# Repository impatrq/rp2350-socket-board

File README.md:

# rp2350-socket-board
Repositorio de la placa de adaptación para el RP2350

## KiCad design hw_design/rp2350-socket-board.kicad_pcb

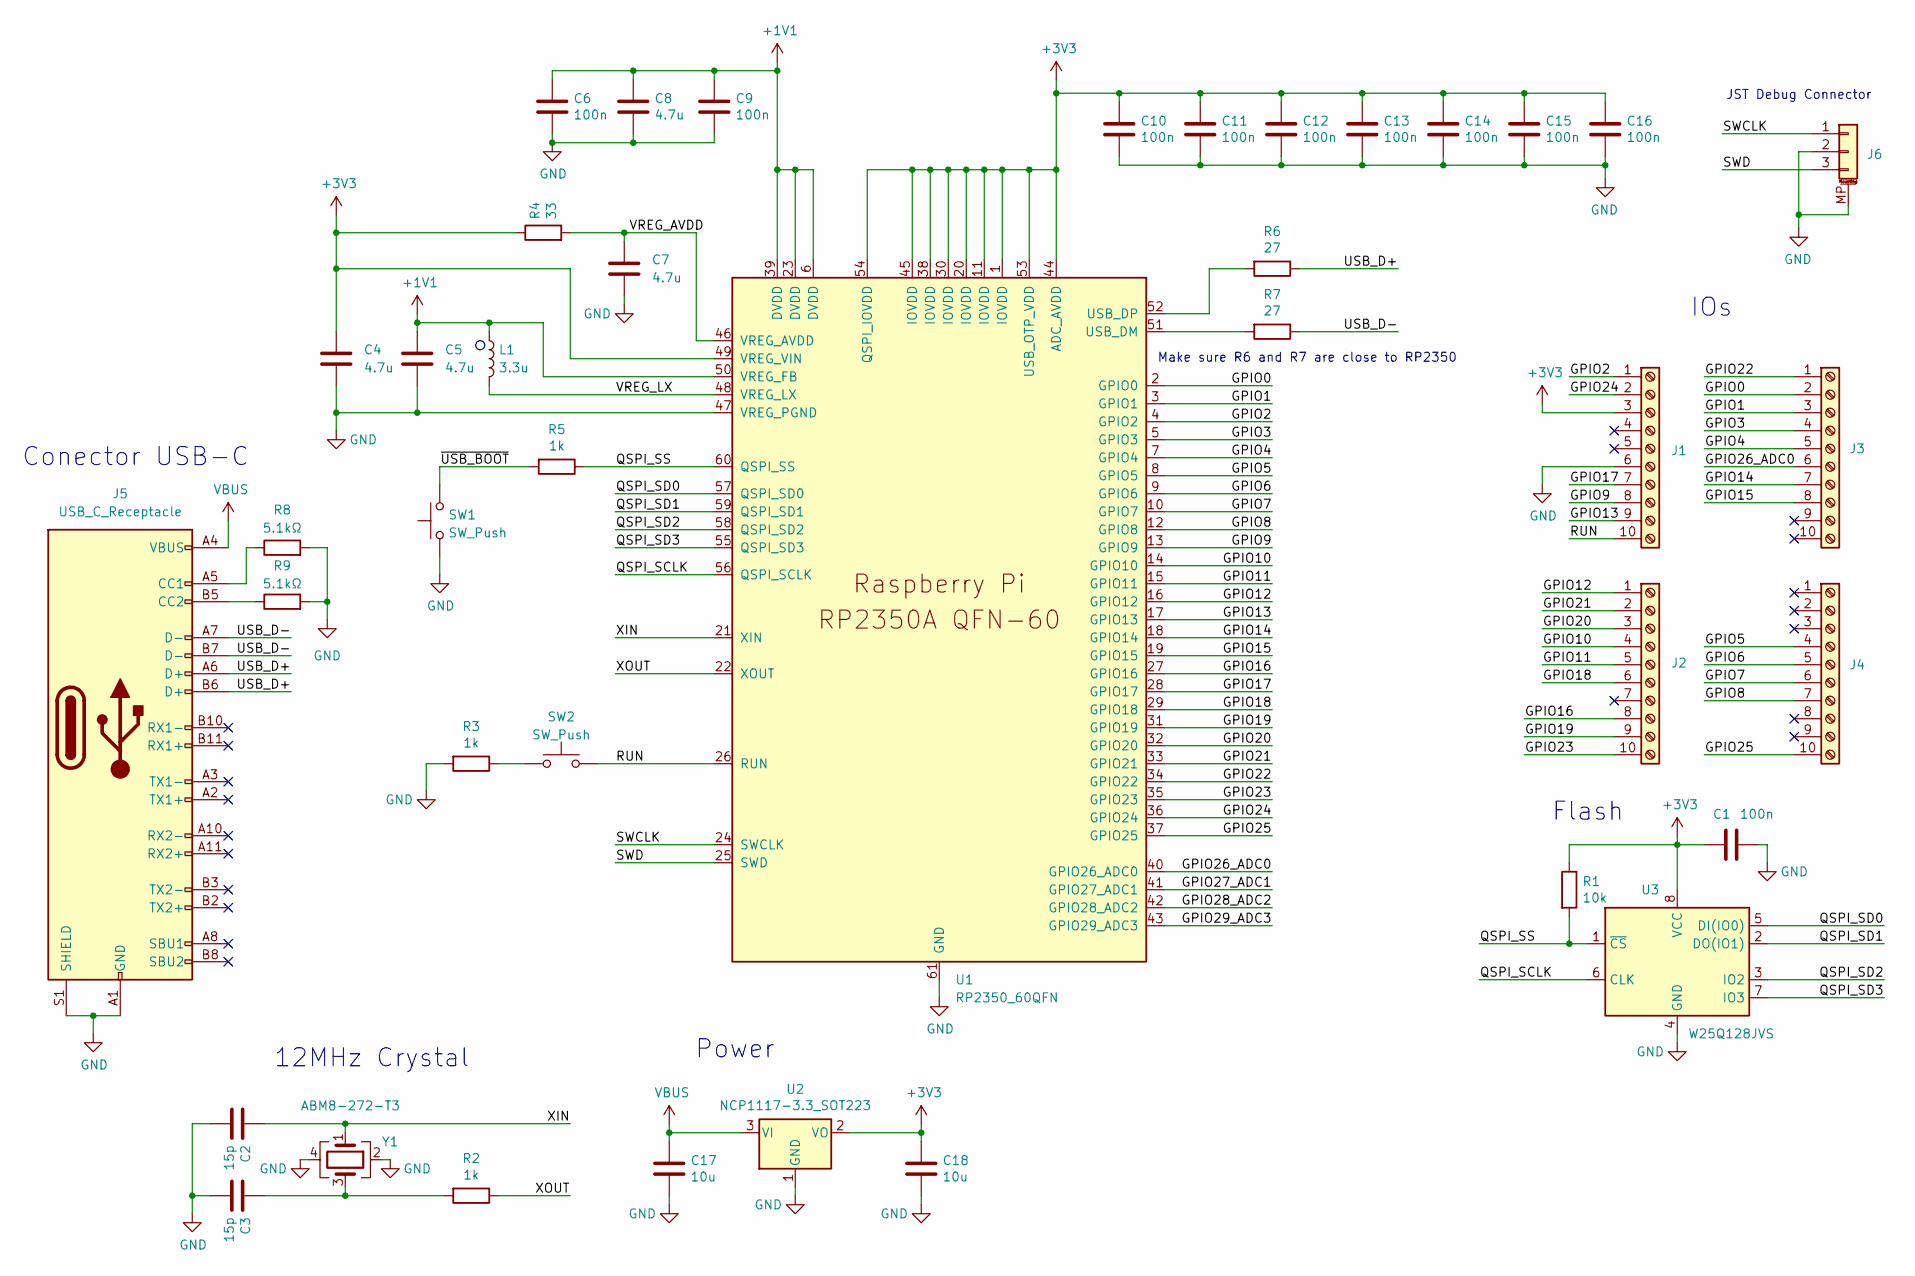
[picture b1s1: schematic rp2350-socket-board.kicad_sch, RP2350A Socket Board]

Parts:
C1, C6, C9, C10, C11, C12, C13, C14, C15, C16: 100n; C_0402_1005Metric_Pad0.74x0.62mm_HandSolder
C2, C3: 15p; C_0402_1005Metric_Pad0.74x0.62mm_HandSolder
C4, C5: 4.7u; C_0402_1005Metric_small_pads
C7, C8: 4.7u; C_0402_1005Metric_Pad0.74x0.62mm_HandSolder
C17, C18: 10u; C_0402_1005Metric_Pad0.74x0.62mm_HandSolder
J1, J2, J3, J4: Screw_Terminal_01x10; PinHeader_1x10_P2.54mm_Vertical
J5: USB_C_Receptacle; USB_C_Receptacle_G-Switch_GT-USB-7010ASV
J6: SM03B-SRSS-TB; PinHeader_1x03_P2.54mm_Vertical
L1: 3.3u; L_pol_2016
R1: 10k; R_0402_1005Metric
R2, R3, R5: 1k; R_0402_1005Metric
R4: 33; R_0402_1005Metric
R6, R7: 27; R_0402_1005Metric
R8, R9: 5.1kΩ; R_0402_1005Metric
SW1, SW2: SW_Push; SW_Push_1P1T_NO_Vertical_Wuerth_434133025816
U1: RP2350_60QFN; RP2350-QFN-60-1EP_7x7_P0.4mm_EP3.4x3.4mm_ThermalVias
U2: NCP1117-3.3_SOT223; SOT-223-3_TabPin2
U3: W25Q128JVS; SOIC-8_5.3x5.3mm_P1.27mm
Y1: ABM8-272-T3; Crystal_SMD_3225-4Pin_3.2x2.5mm

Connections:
+1V1: C5.1, C6.1, C8.1, C9.1, L1.1, U1.6 (DVDD), U1.23 (DVDD), U1.39 (DVDD), U1.50 (VREG_FB)
+3V3: C1.1, C4.1, C10.1, C11.1, C12.1, C13.1, C14.1, C15.1, C16.1, C18.1, J1.3, R1.1, R4.1, U1.1 (IOVDD), U1.11 (IOVDD), U1.20 (IOVDD), U1.30 (IOVDD), U1.38 (IOVDD), U1.44 (ADC_AVDD), U1.45 (IOVDD), U1.49 (VREG_VIN), U1.53 (USB_OTP_VDD), U1.54 (QSPI_IOVDD), U2.2 (VO), U3.8 (VCC)
/GPIO0: J3.2, U1.2 (GPIO0)
/GPIO1: J3.3, U1.3 (GPIO1)
/GPIO2: J1.1, U1.4 (GPIO2)
/GPIO3: J3.4, U1.5 (GPIO3)
/GPIO4: J3.5, U1.7 (GPIO4)
/GPIO5: J4.4, U1.8 (GPIO5)
/GPIO6: J4.5, U1.9 (GPIO6)
/GPIO7: J4.6, U1.10 (GPIO7)
/GPIO8: J4.7, U1.12 (GPIO8)
/GPIO9: J1.8, U1.13 (GPIO9)
/GPIO10: J2.4, U1.14 (GPIO10)
/GPIO11: J2.5, U1.15 (GPIO11)
/GPIO12: J2.1, U1.16 (GPIO12)
/GPIO13: J1.9, U1.17 (GPIO13)
/GPIO14: J3.7, U1.18 (GPIO14)
/GPIO15: J3.8, U1.19 (GPIO15)
/GPIO16: J2.8, U1.27 (GPIO16)
/GPIO17: J1.7, U1.28 (GPIO17)
/GPIO18: J2.6, U1.29 (GPIO18)
/GPIO19: J2.9, U1.31 (GPIO19)
/GPIO20: J2.3, U1.32 (GPIO20)
/GPIO21: J2.2, U1.33 (GPIO21)
/GPIO22: J3.1, U1.34 (GPIO22)
/GPIO23: J2.10, U1.35 (GPIO23)
/GPIO24: J1.2, U1.36 (GPIO24)
/GPIO25: J4.10, U1.37 (GPIO25)
/GPIO26_ADC0: J3.6, U1.40 (GPIO26_ADC0)
/GPIO27_ADC1: U1.41 (GPIO27_ADC1)
/GPIO28_ADC2: U1.42 (GPIO28_ADC2)
/GPIO29_ADC3: U1.43 (GPIO29_ADC3)
/QSPI_SCLK: U1.56 (QSPI_SCLK), U3.6 (CLK)
/QSPI_SD0: U1.57 (QSPI_SD0), U3.5 (DI(IO0))
/QSPI_SD1: U1.59 (QSPI_SD1), U3.2 (DO(IO1))
/QSPI_SD2: U1.58 (QSPI_SD2), U3.3 (IO2)
/QSPI_SD3: U1.55 (QSPI_SD3), U3.7 (IO3)
/QSPI_SS: R1.2, R5.1, U1.60 (QSPI_SS), U3.1 (~CS)
/RUN: J1.10, SW2.2, U1.26 (RUN); also elsewhere on the board
/SWCLK: J6.1, U1.24 (SWCLK)
/SWD: J6.3, U1.25 (SWD)
/USB_D+: J5.A6 (D+), J5.B6 (D+), R6.1
/USB_D-: J5.A7 (D-), J5.B7 (D-), R7.1
/VREG_AVDD: C7.1, R4.2, U1.46 (VREG_AVDD)
/VREG_LX: L1.2, U1.48 (VREG_LX)
/XIN: C2.1, U1.21 (XIN), Y1.1
/XOUT: R2.1, U1.22 (XOUT)
/~USB_BOOT: R5.2, SW1.2; also elsewhere on the board
GND: C1.2, C2.2, C3.2, C4.2, C5.2, C6.2, C7.2, C8.2, C9.2, C10.2, C11.2, C12.2, C13.2, C14.2, C15.2, C16.2, C17.2, C18.2, J1.6, J5.A1 (GND), J5.A12 (GND), J5.B1 (GND), J5.B12 (GND), J5.S1 (SHIELD), J6.2, J6.MP (MountPin), R3.2, R8.2, R9.2, SW1.1, U1.47 (VREG_PGND), U1.61 (GND), U2.1 (GND), U3.4 (GND), Y1.2, Y1.4; also elsewhere on the board
unnamed: C3.1, R2.2, Y1.3
unnamed: J5.A5 (CC1), R8.1
unnamed: J5.B5 (CC2), R9.1
unnamed 52: R3.1, SW2.1; also elsewhere on the board
unnamed: R7.2, U1.51 (USB_DM)
unnamed: R6.2, U1.52 (USB_DP)
VBUS: C17.1, J5.A4 (VBUS), J5.A9 (VBUS), J5.B4 (VBUS), J5.B9 (VBUS), U2.3 (VI)

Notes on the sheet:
Conector USB-C
Make sure R6 and R7 are close to RP2350
JST Debug Connector
12MHz Crystal
Flash
Power
IOs

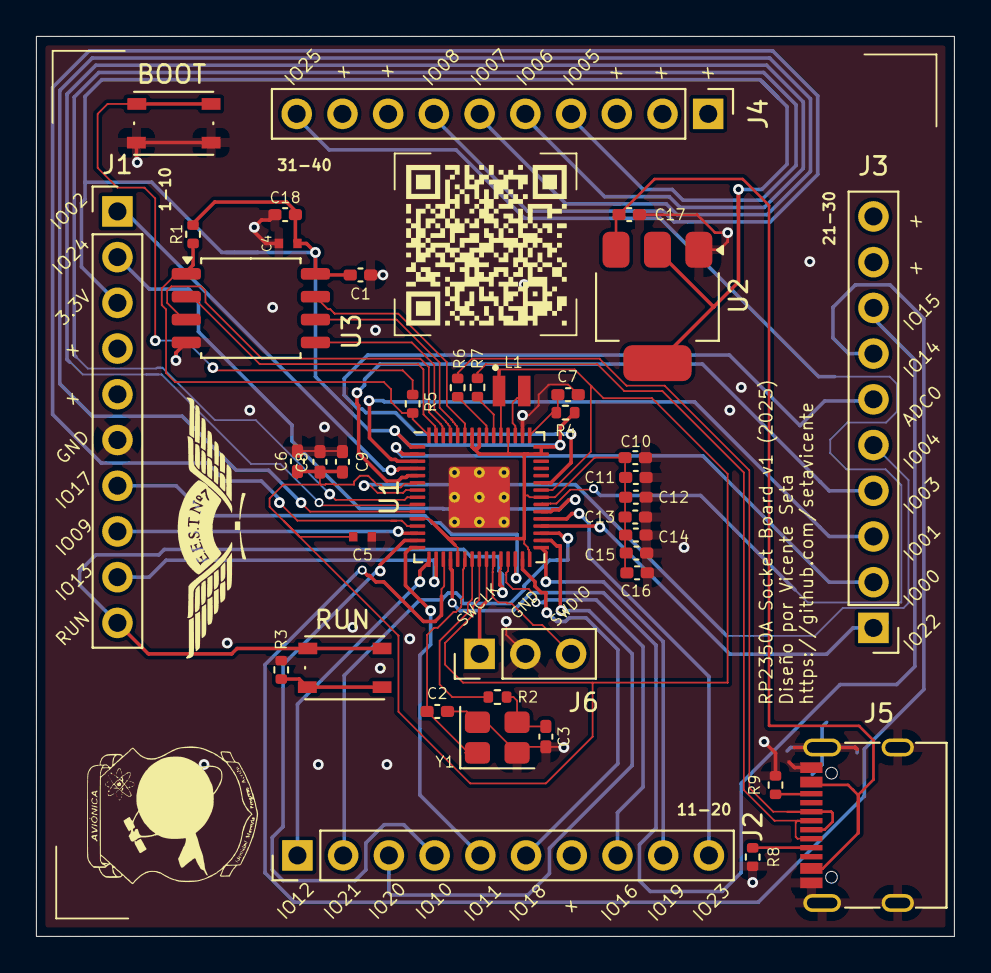
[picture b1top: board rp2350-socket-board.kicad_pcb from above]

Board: 2 copper layers, 51.0 x 50.0 mm, 40 parts (0 on the bottom side), 53 nets.

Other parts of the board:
BOOT: SW_Push; SW_Push_1P1T_NO_Vertical_Wuerth_434133025816
RUN: SW_Push; SW_Push_1P1T_NO_Vertical_Wuerth_434133025816

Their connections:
/RUN: RUN.2; also elsewhere on the board
/~USB_BOOT: BOOT.2; also elsewhere on the board
GND: BOOT.1; also elsewhere on the board
unnamed 52: RUN.1; also elsewhere on the board

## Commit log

2025-07-03 feat: diseño preliminar de pcb
2025-07-03 chore: librerias
2025-07-03 chore: footprints de logos y qr
2025-07-03 chore: ignora directorios no relevantes
2025-07-03 chore: biblioteca de rp2350
